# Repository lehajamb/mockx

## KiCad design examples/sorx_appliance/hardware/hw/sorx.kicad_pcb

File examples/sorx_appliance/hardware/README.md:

# SORX hardware — single-board smart order router appliance (MVP)

Custom carrier board around a Toradex Verdin iMX8M Plus SoM. Hardware design only; no boards exist yet and the OS image is out of scope.

## Status: checkpoint 1 (2026-11-16)

Done: requirements, SoM comparison and pick, block diagram, power budget.
Waiting for sign-off before schematics.

| Path | Contents | State |
|---|---|---|
| `docs/requirements.md` | Requirements derived from the MockX feed and SOR examples | Done |
| `docs/som-comparison.md` | SoM comparison and justification | Done |
| `docs/block-diagram.md`, `docs/block-diagram.svg` | Plane-split block diagram, port map | Done |
| `docs/power-budget.md` | Per-rail budget vs. the USB-C PD contract | Done |
| `tools/` | Scripts that generate the diagram and the budget tables | Done |
| `hw/` | KiCad project, schematics PDF, stackup, Gerbers, drill, pick-and-place, assembly drawings | Not started |
| `mech/` | Outline DXF, board STEP, enclosure STEP/STL/3MF, rack ears | Not started |
| `bom/` | BOM CSV with distributor part numbers, second sources, cost roll-up | Not started |
| `docs/` (rest) | Thermal estimate, bring-up checklist, manufacturing test plan, ERC/DRC waivers, stock check | Not started |

## Status (2026-11-16)

Not ready for fabrication. Schematic (ERC clean), BOM, enclosure and documents are complete. The PCB layout is exported but has unconnected items: see `docs/verification-report.md` and `HANDOFF.md`.

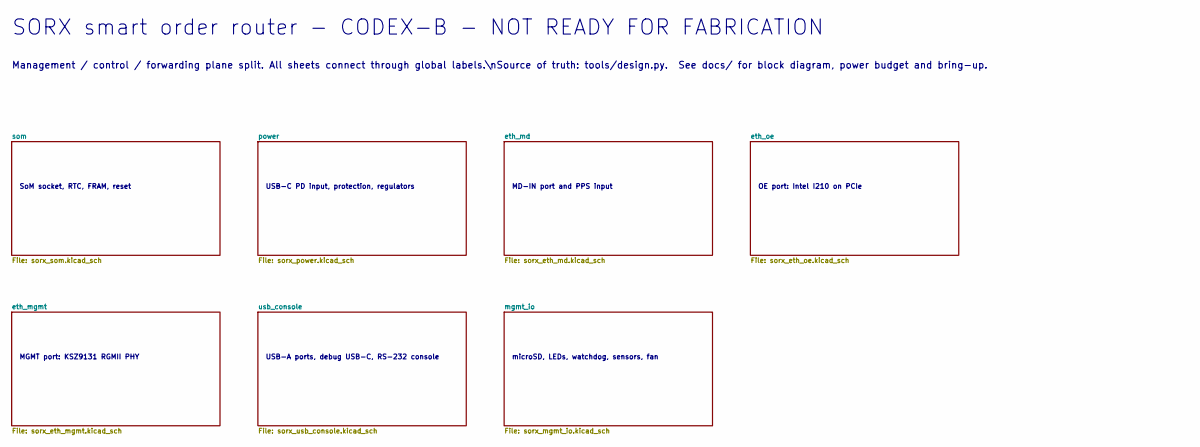
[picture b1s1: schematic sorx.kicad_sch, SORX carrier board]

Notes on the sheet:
SORX smart order router - CODEX-B - NOT READY FOR FABRICATION
Management / control / forwarding plane split. All sheets connect through global labels.\nSource of truth: tools/design.py. See docs/ for block diagram, power budget and bring-up.
SoM socket, RTC, FRAM, reset
USB-C PD input, protection, regulators
MD-IN port and PPS input
OE port: Intel I210 on PCIe
MGMT port: KSZ9131 RGMII PHY
USB-A ports, debug USB-C, RS-232 console
microSD, LEDs, watchdog, sensors, fan

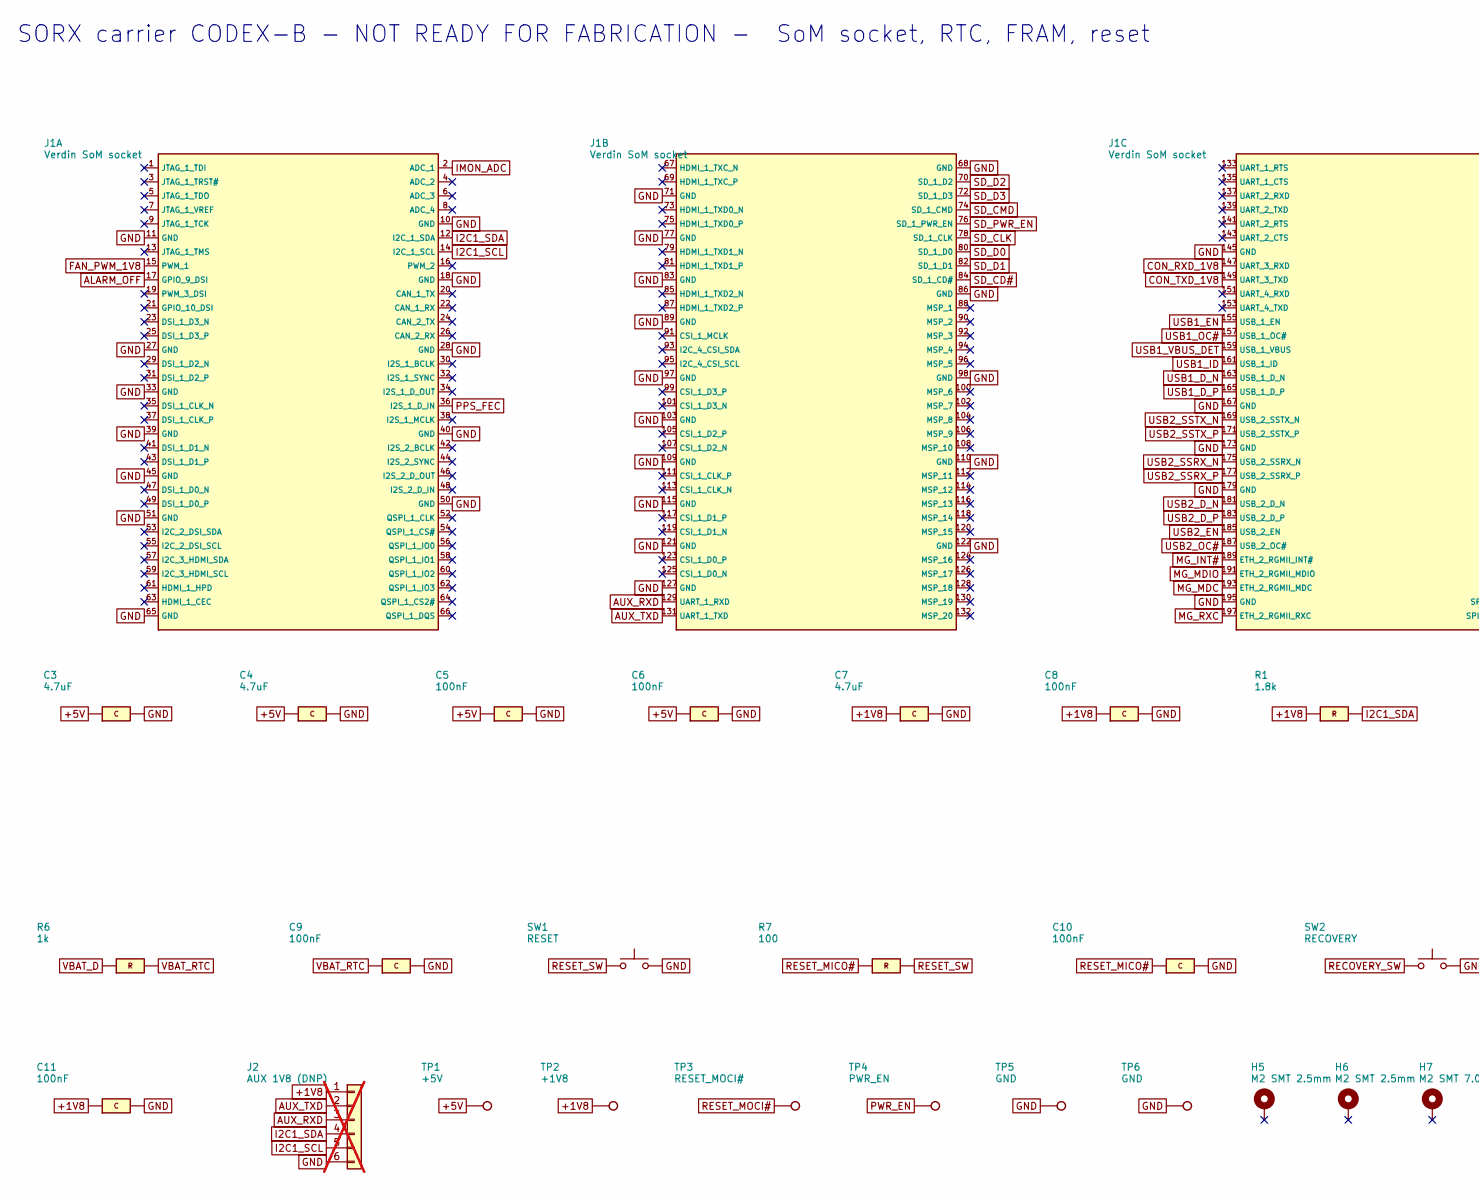
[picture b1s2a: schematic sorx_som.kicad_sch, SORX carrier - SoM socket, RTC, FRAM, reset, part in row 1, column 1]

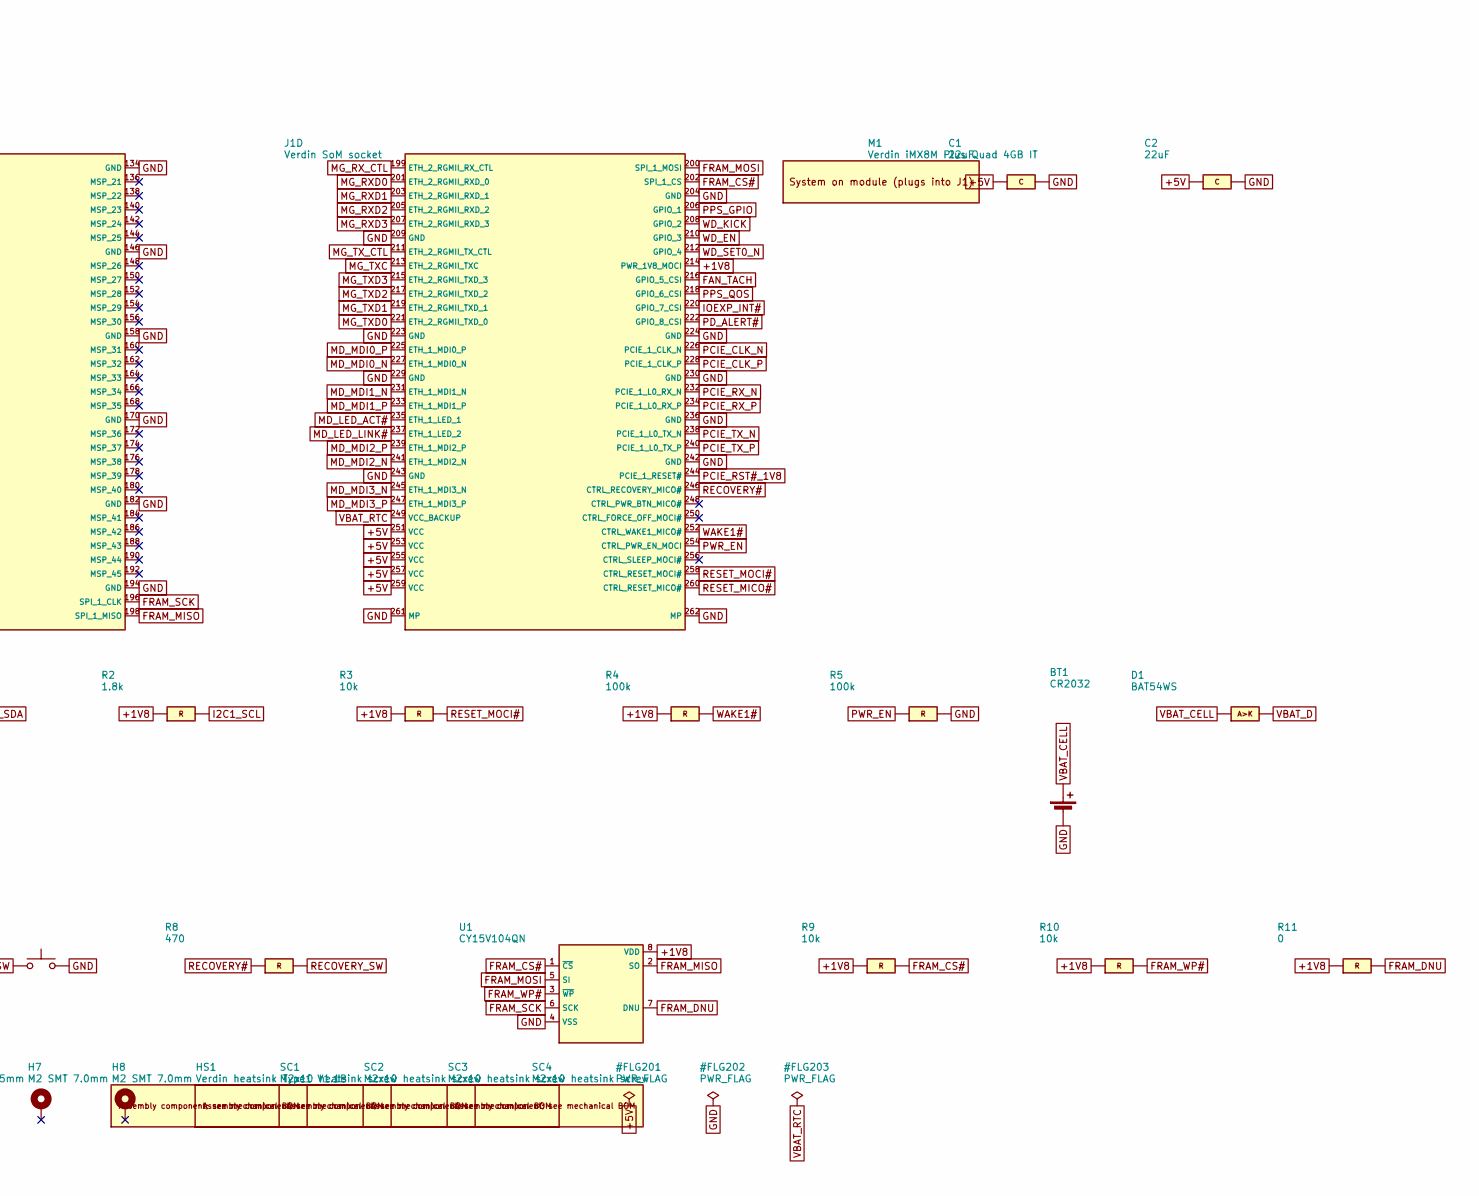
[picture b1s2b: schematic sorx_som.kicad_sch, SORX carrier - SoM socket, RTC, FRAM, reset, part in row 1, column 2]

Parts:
BT1: CR2032; BatteryHolder_Keystone_3034_1x20mm; MPN 3034
C1, C2: 22uF; C_1206_3216Metric; MPN GRM31CR61C226ME15L
C3, C4, C7: 4.7uF; C_0603_1608Metric; MPN GRM188R61A475KE15D
C5, C6, C8, C9, C10, C11: 100nF; C_0402_1005Metric; MPN GRM155R71C104KA88D
D1: BAT54WS; D_SOD-323; MPN BAT54WS-7-F
H5, H6: M2 SMT 2.5mm; Standoff_SMT_M2_WA-SMSI; MPN 9774025243R
H7, H8: M2 SMT 7.0mm; Standoff_SMT_M2_WA-SMSI; MPN 9774070243R
HS1: Verdin heatsink Type1 V1.1B; MPN 23111101
J1: Verdin SoM socket; SODIMM-260_DDR4_TE_2309409-2; MPN 2309409-2
J2: AUX 1V8 (DNP); PinHeader_1x06_P2.54mm_Vertical; MPN 61300611121; not fitted
M1: Verdin iMX8M Plus Quad 4GB IT; MPN 0063
R1, R2: 1.8k; R_0402_1005Metric; MPN RC0402FR-071K8L
R3, R9, R10: 10k; R_0402_1005Metric; MPN RC0402FR-0710KL
R4, R5: 100k; R_0402_1005Metric; MPN RC0402FR-07100KL
R6: 1k; R_0402_1005Metric; MPN RC0402FR-071KL
R7: 100; R_0402_1005Metric; MPN RC0402FR-07100RL
R8: 470; R_0402_1005Metric; MPN RC0402FR-07470RL
R11: 0; R_0402_1005Metric; MPN RC0402JR-070RL
SC1, SC2, SC3, SC4: M2x10 heatsink screw
SW1: RESET; SW_Tactile_SKHH_Angled; MPN SKHHLQA010
SW2: RECOVERY; SW_Tactile_SKHH_Angled; MPN SKHHLQA010
TP1: +5V; TestPoint_Pad_D1.0mm
TP2: +1V8; TestPoint_Pad_D1.0mm
TP3: RESET_MOCI#; TestPoint_Pad_D1.0mm
TP4: PWR_EN; TestPoint_Pad_D1.0mm
TP5, TP6: GND; TestPoint_Pad_D1.0mm
U1: CY15V104QN; SOIC-8_5.23x5.23mm_P1.27mm; MPN CY15V104QN-50SXI

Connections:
+1V8: C7.1, C8.1, C11.1, J1.214 (PWR_1V8_MOCI), J2.1, R1.1, R2.1, R3.1, R4.1, R9.1, R10.1, R11.1, TP2.1, U1.8 (VDD); also elsewhere on the board
+5V: C1.1, C2.1, C3.1, C4.1, C5.1, C6.1, J1.251 (VCC), J1.253 (VCC), J1.255 (VCC), J1.257 (VCC), J1.259 (VCC), TP1.1; also elsewhere on the board
ALARM_OFF: J1.17 (GPIO_9_DSI); also elsewhere on the board
AUX_RXD: J1.129 (UART_1_RXD), J2.3
AUX_TXD: J1.131 (UART_1_TXD), J2.2
CON_RXD_1V8: J1.147 (UART_3_RXD); also elsewhere on the board
CON_TXD_1V8: J1.149 (UART_3_TXD); also elsewhere on the board
FAN_PWM_1V8: J1.15 (PWM_1); also elsewhere on the board
FAN_TACH: J1.216 (GPIO_5_CSI); also elsewhere on the board
FRAM_CS#: J1.202 (SPI_1_CS), R9.2, U1.1 (~CS)
FRAM_DNU: R11.2, U1.7 (DNU)
FRAM_MISO: J1.198 (SPI_1_MISO), U1.2 (SO)
FRAM_MOSI: J1.200 (SPI_1_MOSI), U1.5 (SI)
FRAM_SCK: J1.196 (SPI_1_CLK), U1.6 (SCK)
FRAM_WP#: R10.2, U1.3 (~WP)
GND: BT1.2 (-), C1.2, C2.2, C3.2, C4.2, C5.2, C6.2, C7.2, C8.2, C9.2, C10.2, C11.2, J1.10 (GND), J1.11 (GND), J1.18 (GND), J1.27 (GND), J1.28 (GND), J1.33 (GND), J1.39 (GND), J1.40 (GND), J1.45 (GND), J1.50 (GND), J1.51 (GND), J1.65 (GND), J1.68 (GND), J1.71 (GND), J1.77 (GND), J1.83 (GND), J1.86 (GND), J1.89 (GND), J1.97 (GND), J1.98 (GND), J1.103 (GND), J1.109 (GND), J1.110 (GND), J1.115 (GND), J1.121 (GND), J1.122 (GND), J1.127 (GND), J1.134 (GND), J1.145 (GND), J1.146 (GND), J1.158 (GND), J1.167 (GND), J1.170 (GND), J1.173 (GND), J1.179 (GND), J1.182 (GND), J1.194 (GND), J1.195 (GND), J1.204 (GND), J1.209 (GND), J1.223 (GND), J1.224 (GND), J1.229 (GND), J1.230 (GND), J1.236 (GND), J1.242 (GND), J1.243 (GND), J1.261 (MP), J1.262 (MP), J2.6, R5.2, SW1.2, SW2.2, TP5.1, TP6.1, U1.4 (VSS); also elsewhere on the board
I2C1_SCL: J1.14 (I2C_1_SCL), J2.5, R2.2; also elsewhere on the board
I2C1_SDA: J1.12 (I2C_1_SDA), J2.4, R1.2; also elsewhere on the board
IMON_ADC: J1.2 (ADC_1); also elsewhere on the board
IOEXP_INT#: J1.220 (GPIO_7_CSI); also elsewhere on the board
MD_LED_ACT#: J1.235 (ETH_1_LED_1); also elsewhere on the board
MD_LED_LINK#: J1.237 (ETH_1_LED_2); also elsewhere on the board
MD_MDI0_N: J1.227 (ETH_1_MDI0_N); also elsewhere on the board
MD_MDI0_P: J1.225 (ETH_1_MDI0_P); also elsewhere on the board
MD_MDI1_N: J1.231 (ETH_1_MDI1_N); also elsewhere on the board
MD_MDI1_P: J1.233 (ETH_1_MDI1_P); also elsewhere on the board
MD_MDI2_N: J1.241 (ETH_1_MDI2_N); also elsewhere on the board
MD_MDI2_P: J1.239 (ETH_1_MDI2_P); also elsewhere on the board
MD_MDI3_N: J1.245 (ETH_1_MDI3_N); also elsewhere on the board
MD_MDI3_P: J1.247 (ETH_1_MDI3_P); also elsewhere on the board
MG_INT#: J1.189 (ETH_2_RGMII_INT#); also elsewhere on the board
MG_MDC: J1.193 (ETH_2_RGMII_MDC); also elsewhere on the board
MG_MDIO: J1.191 (ETH_2_RGMII_MDIO); also elsewhere on the board
MG_RXC: J1.197 (ETH_2_RGMII_RXC); also elsewhere on the board
MG_RXD0: J1.201 (ETH_2_RGMII_RXD_0); also elsewhere on the board
MG_RXD1: J1.203 (ETH_2_RGMII_RXD_1); also elsewhere on the board
MG_RXD2: J1.205 (ETH_2_RGMII_RXD_2); also elsewhere on the board
MG_RXD3: J1.207 (ETH_2_RGMII_RXD_3); also elsewhere on the board
MG_RX_CTL: J1.199 (ETH_2_RGMII_RX_CTL); also elsewhere on the board
MG_TXC: J1.213 (ETH_2_RGMII_TXC); also elsewhere on the board
MG_TXD0: J1.221 (ETH_2_RGMII_TXD_0); also elsewhere on the board
MG_TXD1: J1.219 (ETH_2_RGMII_TXD_1); also elsewhere on the board
MG_TXD2: J1.217 (ETH_2_RGMII_TXD_2); also elsewhere on the board
MG_TXD3: J1.215 (ETH_2_RGMII_TXD_3); also elsewhere on the board
MG_TX_CTL: J1.211 (ETH_2_RGMII_TX_CTL); also elsewhere on the board
PCIE_CLK_N: J1.226 (PCIE_1_CLK_N); also elsewhere on the board
PCIE_CLK_P: J1.228 (PCIE_1_CLK_P); also elsewhere on the board
PCIE_RST#_1V8: J1.244 (PCIE_1_RESET#); also elsewhere on the board
PCIE_RX_N: J1.232 (PCIE_1_L0_RX_N); also elsewhere on the board
PCIE_RX_P: J1.234 (PCIE_1_L0_RX_P); also elsewhere on the board
PCIE_TX_N: J1.238 (PCIE_1_L0_TX_N); also elsewhere on the board
PCIE_TX_P: J1.240 (PCIE_1_L0_TX_P); also elsewhere on the board
PD_ALERT#: J1.222 (GPIO_8_CSI); also elsewhere on the board
PPS_FEC: J1.36 (I2S_1_D_IN); also elsewhere on the board
PPS_GPIO: J1.206 (GPIO_1); also elsewhere on the board
PPS_QOS: J1.218 (GPIO_6_CSI); also elsewhere on the board
PWR_EN: J1.254 (CTRL_PWR_EN_MOCI), R5.1, TP4.1; also elsewhere on the board
RECOVERY#: J1.246 (CTRL_RECOVERY_MICO#), R8.1; also elsewhere on the board
RECOVERY_SW: R8.2, SW2.1
RESET_MICO#: C10.1, J1.260 (CTRL_RESET_MICO#), R7.1; also elsewhere on the board
RESET_MOCI#: J1.258 (CTRL_RESET_MOCI#), R3.2, TP3.1; also elsewhere on the board
RESET_SW: R7.2, SW1.1
SD_CD#: J1.84 (SD_1_CD#); also elsewhere on the board
SD_CLK: J1.78 (SD_1_CLK); also elsewhere on the board
SD_CMD: J1.74 (SD_1_CMD); also elsewhere on the board
SD_D0: J1.80 (SD_1_D0); also elsewhere on the board
SD_D1: J1.82 (SD_1_D1); also elsewhere on the board
SD_D2: J1.70 (SD_1_D2); also elsewhere on the board
SD_D3: J1.72 (SD_1_D3); also elsewhere on the board
SD_PWR_EN: J1.76 (SD_1_PWR_EN); also elsewhere on the board
USB1_D_N: J1.163 (USB_1_D_N); also elsewhere on the board
USB1_D_P: J1.165 (USB_1_D_P); also elsewhere on the board
USB1_EN: J1.155 (USB_1_EN); also elsewhere on the board
USB1_ID: J1.161 (USB_1_ID); also elsewhere on the board
USB1_OC#: J1.157 (USB_1_OC#); also elsewhere on the board
USB1_VBUS_DET: J1.159 (USB_1_VBUS); also elsewhere on the board
USB2_D_N: J1.181 (USB_2_D_N); also elsewhere on the board
USB2_D_P: J1.183 (USB_2_D_P); also elsewhere on the board
USB2_EN: J1.185 (USB_2_EN); also elsewhere on the board
USB2_OC#: J1.187 (USB_2_OC#); also elsewhere on the board
USB2_SSRX_N: J1.175 (USB_2_SSRX_N); also elsewhere on the board
USB2_SSRX_P: J1.177 (USB_2_SSRX_P); also elsewhere on the board
USB2_SSTX_N: J1.169 (USB_2_SSTX_N); also elsewhere on the board
USB2_SSTX_P: J1.171 (USB_2_SSTX_P); also elsewhere on the board
VBAT_CELL: BT1.1 (+), D1.2 (A)
VBAT_D: D1.1 (K), R6.1
VBAT_RTC: C9.1, J1.249 (VCC_BACKUP), R6.2
WAKE1#: J1.252 (CTRL_WAKE1_MICO#), R4.2
WD_EN: J1.210 (GPIO_3); also elsewhere on the board
WD_KICK: J1.208 (GPIO_2); also elsewhere on the board
WD_SET0_N: J1.212 (GPIO_4); also elsewhere on the board

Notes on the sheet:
SORX carrier CODEX-B - NOT READY FOR FABRICATION - SoM socket, RTC, FRAM, reset

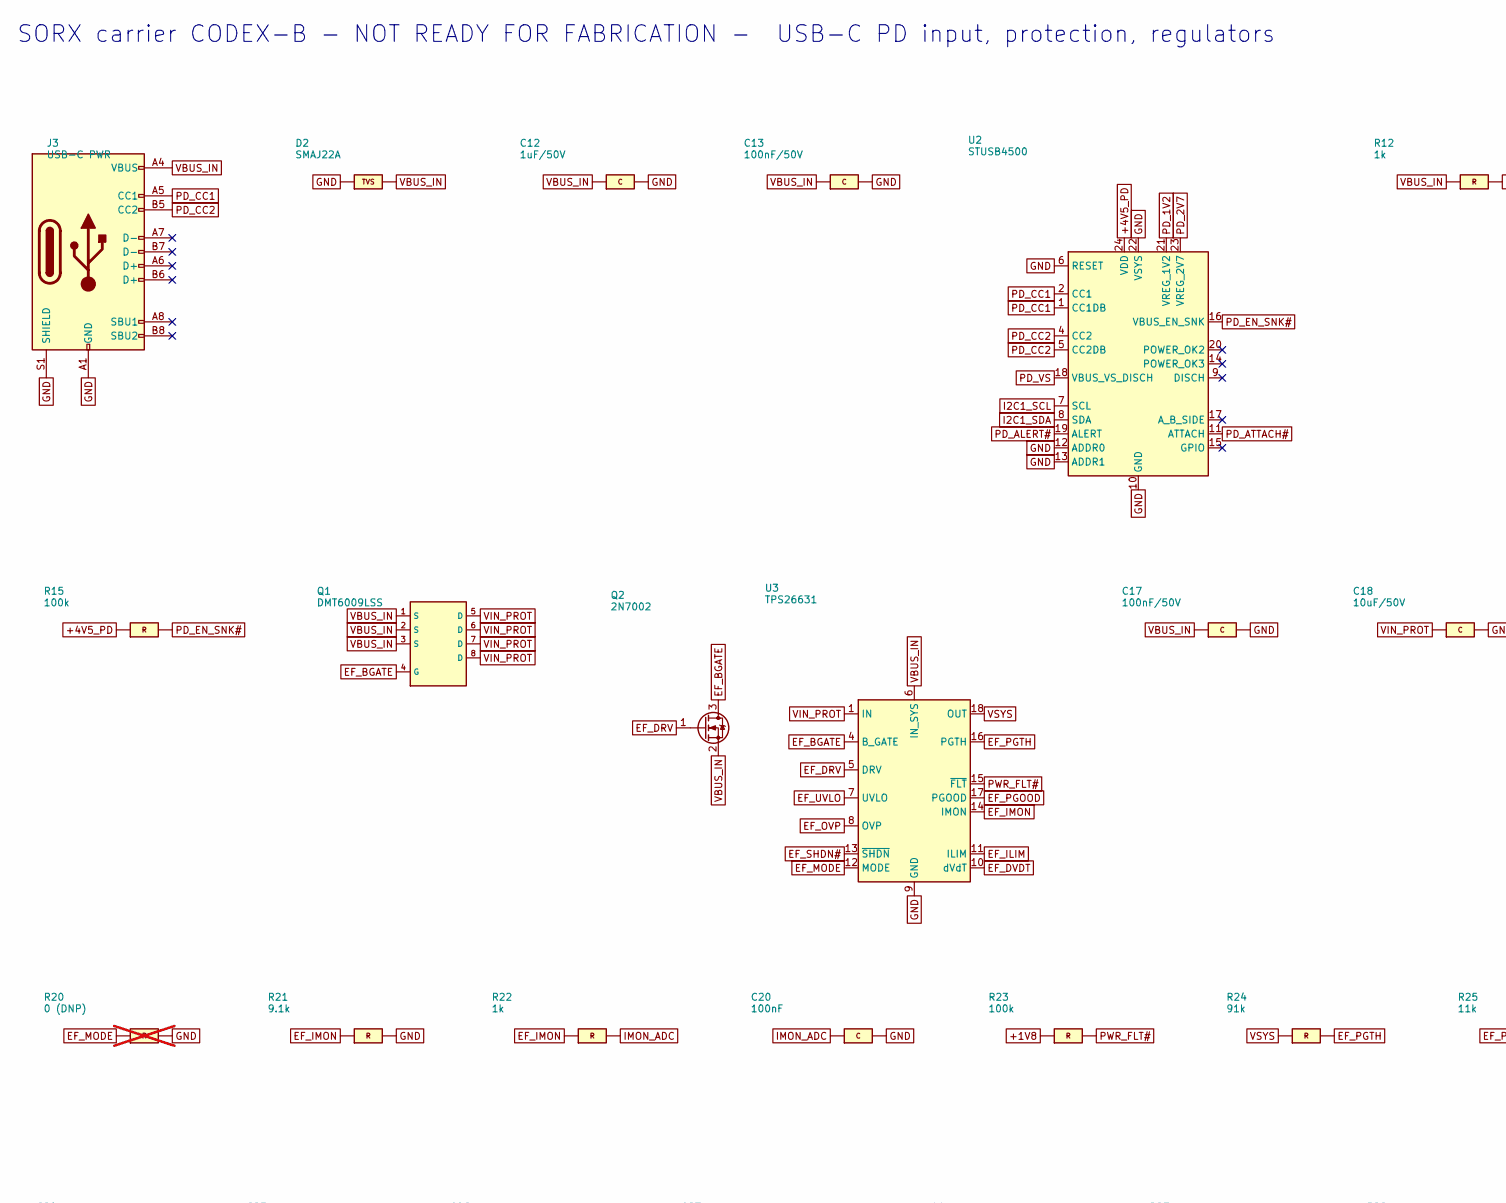
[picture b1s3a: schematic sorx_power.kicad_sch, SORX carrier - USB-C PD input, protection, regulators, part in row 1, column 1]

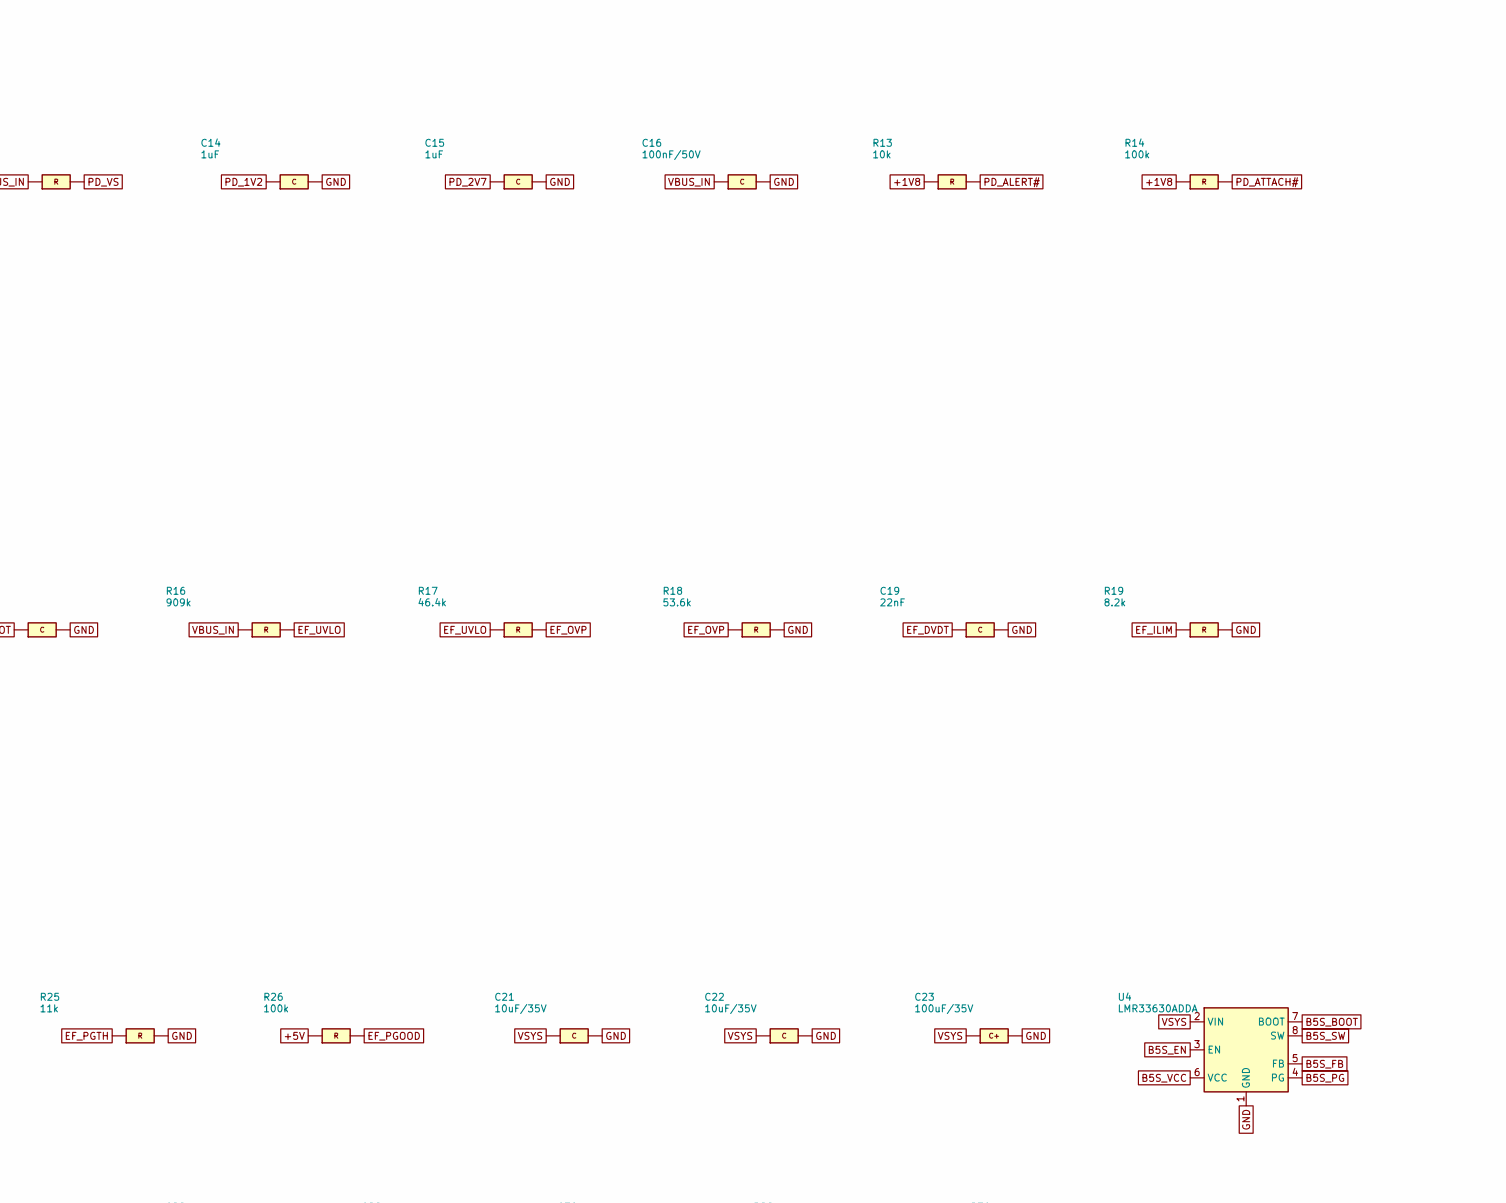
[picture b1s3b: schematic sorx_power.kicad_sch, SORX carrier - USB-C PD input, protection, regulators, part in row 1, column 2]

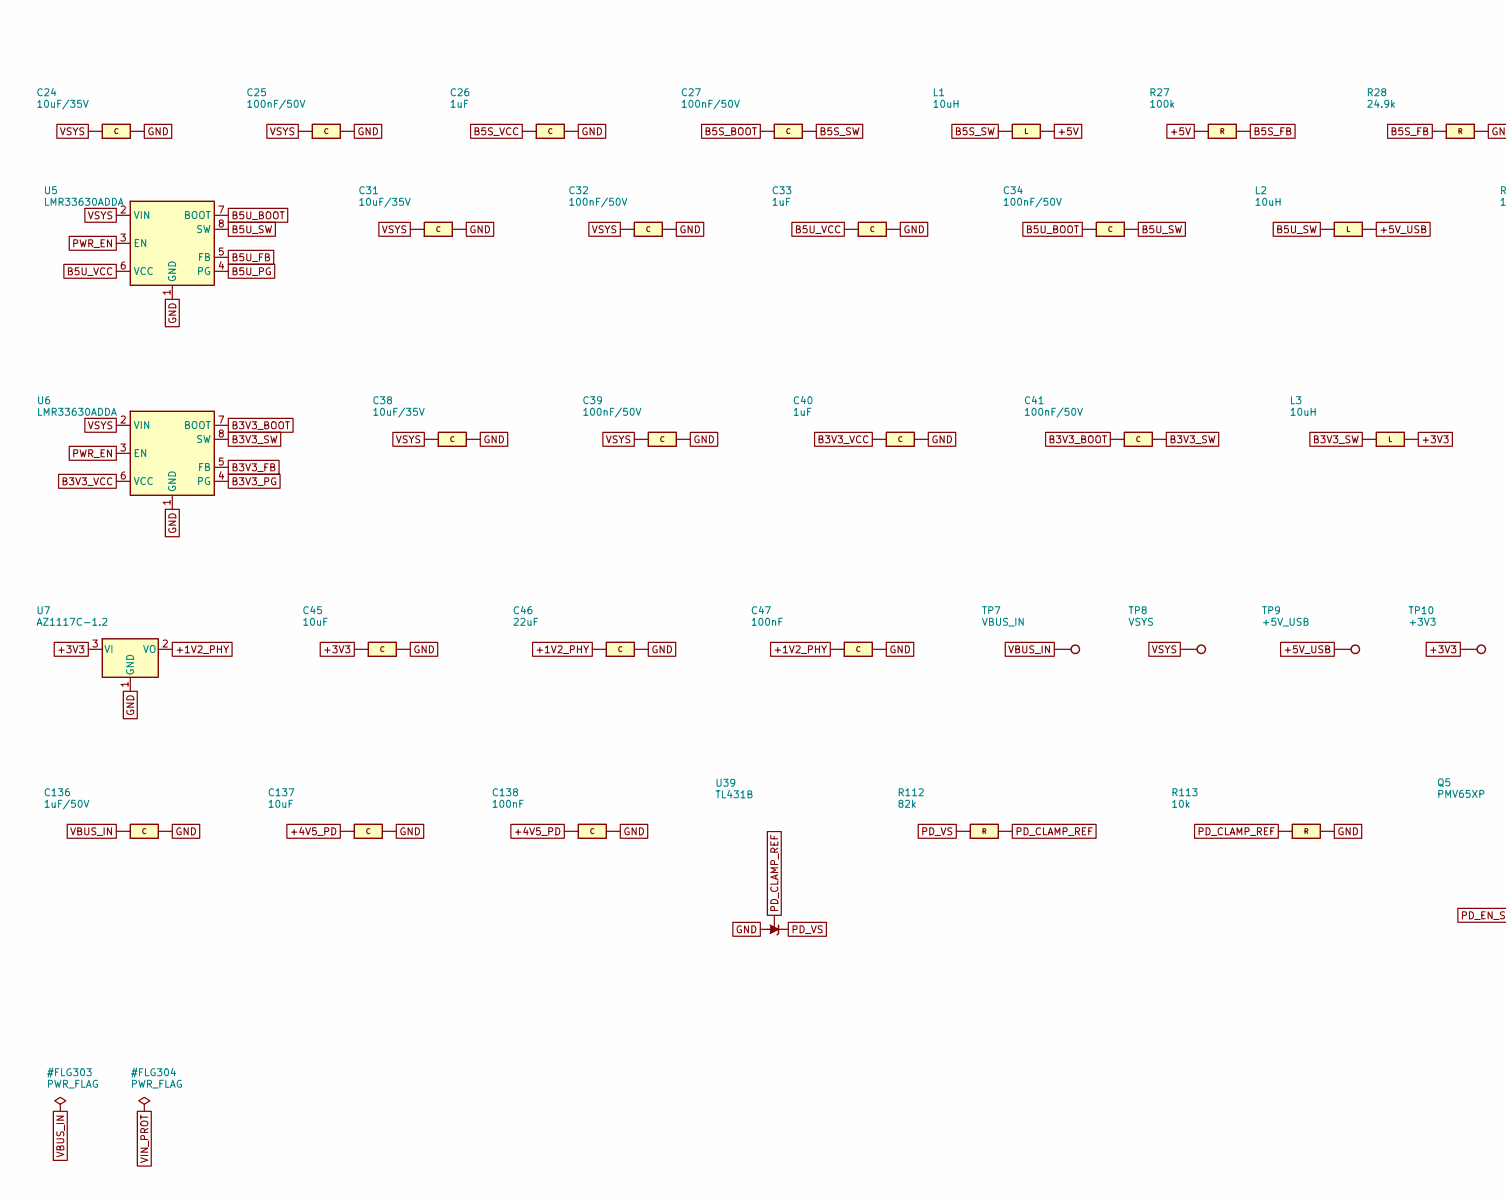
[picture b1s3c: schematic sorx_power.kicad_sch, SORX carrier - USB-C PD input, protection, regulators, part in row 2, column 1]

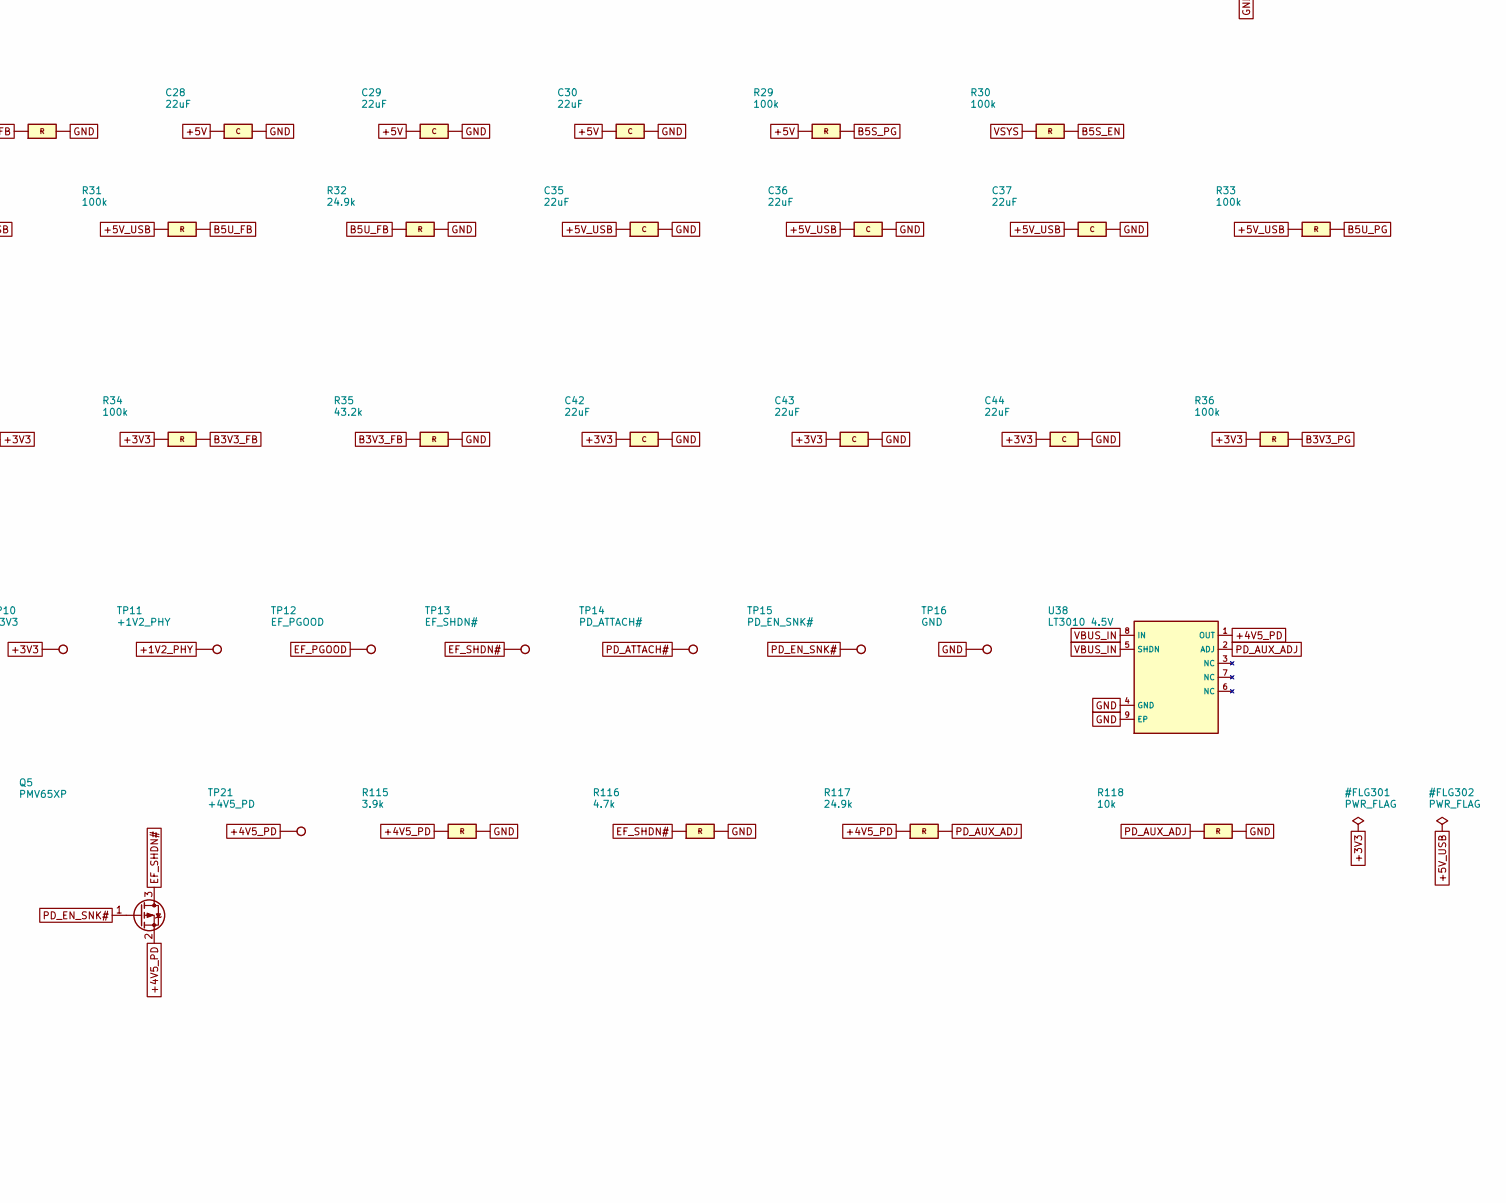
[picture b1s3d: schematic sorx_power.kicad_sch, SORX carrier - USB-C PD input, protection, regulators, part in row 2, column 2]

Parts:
C12, C136: 1uF/50V; C_0805_2012Metric; MPN GRM21BR71H105KA12L
C13, C16, C17, C25, C27, C32, C34, C39, C41: 100nF/50V; C_0603_1608Metric; MPN GRM188R71H104KA93D
C14, C15, C26, C33, C40: 1uF; C_0603_1608Metric; MPN GRM188R61E105KA12D
C18: 10uF/50V; C_1210_3225Metric; MPN GRM32ER71H106KA12L
C19: 22nF; C_0402_1005Metric; MPN GRM155R71H223KA12D
C20, C47, C138: 100nF; C_0402_1005Metric; MPN GRM155R71C104KA88D
C21, C22, C24, C31, C38: 10uF/35V; C_1210_3225Metric; MPN GRM32ER7YA106KA12L
C23: 100uF/35V; CP_Elec_6.3x7.7; MPN EEE-FK1V101XP
C28, C29, C30, C35, C36, C37, C42, C43, C44, C46: 22uF; C_1206_3216Metric; MPN GRM31CR61C226ME15L
C45, C137: 10uF; C_0805_2012Metric; MPN GRM21BR61A106KE19L
D2: SMAJ22A; D_SMA; MPN SMAJ22A
J3: USB-C PWR; USB_C_Receptacle_GCT_USB4105-xx-A_16P_TopMnt_Horizontal; MPN USB4105-GF-A
L1, L2, L3: 10uH; L_Coilcraft_XAL5050-XXX; MPN XAL5050-103MEC
Q1: DMT6009LSS; SOIC-8_3.9x4.9mm_P1.27mm; MPN DMT6009LSS-13
Q2: 2N7002; SOT-23; MPN 2N7002-7-F
Q5: PMV65XP; SOT-23; MPN PMV65XP,215
R12: 1k; R_1206_3216Metric; MPN RC1206FR-071KL
R13, R113, R118: 10k; R_0402_1005Metric; MPN RC0402FR-0710KL
R14, R15, R23, R26, R27, R29, R30, R31, R33, R34, R36: 100k; R_0402_1005Metric; MPN RC0402FR-07100KL
R16: 909k; R_0402_1005Metric; MPN RC0402FR-07909KL
R17: 46.4k; R_0402_1005Metric; MPN RC0402FR-0746K4L
R18: 53.6k; R_0402_1005Metric; MPN RC0402FR-0753K6L
R19: 8.2k; R_0402_1005Metric; MPN RC0402FR-078K2L
R20: 0 (DNP); R_0402_1005Metric; MPN RC0402JR-070RL; not fitted
R21: 9.1k; R_0402_1005Metric; MPN RC0402FR-079K1L
R22: 1k; R_0402_1005Metric; MPN RC0402FR-071KL
R24: 91k; R_0402_1005Metric; MPN RC0402FR-0791KL
R25: 11k; R_0402_1005Metric; MPN RC0402FR-0711KL
R28, R32, R117: 24.9k; R_0402_1005Metric; MPN RC0402FR-0724K9L
R35: 43.2k; R_0402_1005Metric; MPN RC0402FR-0743K2L
R112: 82k; R_0402_1005Metric; MPN RC0402FR-0782KL
R115: 3.9k; R_0402_1005Metric; MPN RC0402FR-073K9L
R116: 4.7k; R_0402_1005Metric; MPN RC0402FR-074K7L
TP7: VBUS_IN; TestPoint_Pad_D1.0mm
TP8: VSYS; TestPoint_Pad_D1.0mm
TP9: +5V_USB; TestPoint_Pad_D1.0mm
TP10: +3V3; TestPoint_Pad_D1.0mm
TP11: +1V2_PHY; TestPoint_Pad_D1.0mm
TP12: EF_PGOOD; TestPoint_Pad_D1.0mm
TP13: EF_SHDN#; TestPoint_Pad_D1.0mm
TP14: PD_ATTACH#; TestPoint_Pad_D1.0mm
TP15: PD_EN_SNK#; TestPoint_Pad_D1.0mm
TP16: GND; TestPoint_Pad_D1.0mm
TP21: +4V5_PD; TestPoint_Pad_D1.0mm
U2: STUSB4500; QFN-24-1EP_4x4mm_P0.5mm_EP2.7x2.7mm; MPN STUSB4500QTR
U3: TPS26631; HTSSOP-20-1EP_4.4x6.5mm_P0.65mm_EP3.4x6.5mm_Mask2.96x2.96mm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; MPN TPS26631PWPR
U4, U5, U6: LMR33630ADDA; Texas_HSOP-8-1EP_3.9x4.9mm_P1.27mm_ThermalVias; MPN LMR33630ADDAR
U7: AZ1117C-1.2; SOT-223-3_TabPin2; MPN AZ1117CH-1.2TRG1
U38: LT3010 4.5V; LT_MS8E; MPN LT3010EMS8E#PBF
U39: TL431B; SOT-89-3; MPN TL431BIPK

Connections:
+1V2_PHY: C46.1, C47.1, TP11.1, U7.2 (VO); also elsewhere on the board
+1V8: R13.1, R14.1, R23.1; also elsewhere on the board
+3V3: C42.1, C43.1, C44.1, C45.1, L3.2, R34.1, R36.1, TP10.1, U7.3 (VI); also elsewhere on the board
+4V5_PD: C137.1, C138.1, Q5.2 (S), R15.1, R115.1, R117.1, TP21.1, U2.24 (VDD), U38.1 (OUT)
+5V: C28.1, C29.1, C30.1, L1.2, R26.1, R27.1, R29.1; also elsewhere on the board
+5V_USB: C35.1, C36.1, C37.1, L2.2, R31.1, R33.1, TP9.1; also elsewhere on the board
B3V3_BOOT: C41.1, U6.7 (BOOT)
B3V3_FB: R34.2, R35.1, U6.5 (FB)
B3V3_PG: R36.2, U6.4 (PG)
B3V3_SW: C41.2, L3.1, U6.8 (SW)
B3V3_VCC: C40.1, U6.6 (VCC)
B5S_BOOT: C27.1, U4.7 (BOOT)
B5S_EN: R30.2, U4.3 (EN)
B5S_FB: R27.2, R28.1, U4.5 (FB)
B5S_PG: R29.2, U4.4 (PG)
B5S_SW: C27.2, L1.1, U4.8 (SW)
B5S_VCC: C26.1, U4.6 (VCC)
B5U_BOOT: C34.1, U5.7 (BOOT)
B5U_FB: R31.2, R32.1, U5.5 (FB)
B5U_PG: R33.2, U5.4 (PG)
B5U_SW: C34.2, L2.1, U5.8 (SW)
B5U_VCC: C33.1, U5.6 (VCC)
EF_BGATE: Q1.4 (G), Q2.3 (D), U3.4 (B_GATE)
EF_DRV: Q2.1 (G), U3.5 (DRV)
EF_DVDT: C19.1, U3.10 (dVdT)
EF_ILIM: R19.1, U3.11 (ILIM)
EF_IMON: R21.1, R22.1, U3.14 (IMON)
EF_MODE: R20.1, U3.12 (MODE)
EF_OVP: R17.2, R18.1, U3.8 (OVP)
EF_PGOOD: R26.2, TP12.1, U3.17 (PGOOD)
EF_PGTH: R24.2, R25.1, U3.16 (PGTH)
EF_SHDN#: Q5.3 (D), R116.1, TP13.1, U3.13 (~SHDN)
EF_UVLO: R16.2, R17.1, U3.7 (UVLO)
GND: C12.2, C13.2, C14.2, C15.2, C16.2, C17.2, C18.2, C19.2, C20.2, C21.2, C22.2, C23.2 (-), C24.2, C25.2, C26.2, C28.2, C29.2, C30.2, C31.2, C32.2, C33.2, C35.2, C36.2, C37.2, C38.2, C39.2, C40.2, C42.2, C43.2, C44.2, C45.2, C46.2, C47.2, C136.2, C137.2, C138.2, D2.2 (A), J3.A1 (GND), J3.A12 (GND), J3.B1 (GND), J3.B12 (GND), J3.S1 (SHIELD), R18.2, R19.2, R20.2, R21.2, R25.2, R28.2, R32.2, R35.2, R113.2, R115.2, R116.2, R118.2, TP16.1, U2.6 (RESET), U2.10 (GND), U2.12 (ADDR0), U2.13 (ADDR1), U2.22 (VSYS), U2.25 (GND), U3.9 (GND), U3.21 (GND), U4.1 (GND), U4.9 (GND), U5.1 (GND), U5.9 (GND), U6.1 (GND), U6.9 (GND), U7.1 (GND), U38.4 (GND), U38.9 (EP), U39.2 (A); also elsewhere on the board
I2C1_SCL: U2.7 (SCL); also elsewhere on the board
I2C1_SDA: U2.8 (SDA); also elsewhere on the board
IMON_ADC: C20.1, R22.2; also elsewhere on the board
PD_1V2: C14.1, U2.21 (VREG_1V2)
PD_2V7: C15.1, U2.23 (VREG_2V7)
PD_ALERT#: R13.2, U2.19 (ALERT); also elsewhere on the board
PD_ATTACH#: R14.2, TP14.1, U2.11 (ATTACH); also elsewhere on the board
PD_AUX_ADJ: R117.2, R118.1, U38.2 (ADJ)
PD_CC1: J3.A5 (CC1), U2.1 (CC1DB), U2.2 (CC1)
PD_CC2: J3.B5 (CC2), U2.4 (CC2), U2.5 (CC2DB)
PD_CLAMP_REF: R112.2, R113.1, U39.1 (REF)
PD_EN_SNK#: Q5.1 (G), R15.2, TP15.1, U2.16 (VBUS_EN_SNK)
PD_VS: R12.2, R112.1, U2.18 (VBUS_VS_DISCH), U39.3 (K)
PWR_EN: U5.3 (EN), U6.3 (EN); also elsewhere on the board
PWR_FLT#: R23.2, U3.15 (~FLT); also elsewhere on the board
VBUS_IN: C12.1, C13.1, C16.1, C17.1, C136.1, D2.1 (K), J3.A4 (VBUS), J3.A9 (VBUS), J3.B4 (VBUS), J3.B9 (VBUS), Q1.1 (S), Q1.2 (S), Q1.3 (S), Q2.2 (S), R12.1, R16.1, TP7.1, U3.6 (IN_SYS), U38.5 (SHDN), U38.8 (IN)
VIN_PROT: C18.1, Q1.5 (D), Q1.6 (D), Q1.7 (D), Q1.8 (D), U3.1 (IN), U3.2 (IN), U3.3 (IN)
VSYS: C21.1, C22.1, C23.1 (+), C24.1, C25.1, C31.1, C32.1, C38.1, C39.1, R24.1, R30.1, TP8.1, U3.18 (OUT), U3.19 (OUT), U3.20 (OUT), U4.2 (VIN), U5.2 (VIN), U6.2 (VIN)

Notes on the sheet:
SORX carrier CODEX-B - NOT READY FOR FABRICATION - USB-C PD input, protection, regulators
